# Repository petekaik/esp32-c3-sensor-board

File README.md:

# ESP32-C3 Sensor Carrier Board

Wall-mountable carrier for an **ESP32-C3 Super Mini** that exposes the module's GPIO, power and
comms for plug-in sensor and peripheral modules. Hardware only — the ESPHome configuration lives
in a separate project (`doorbell.yml` is the authoritative pin/feature map).

Current board: **rev2, 46 × 89 mm**, 2-layer, USB-C on the top short edge.

## Modules

| Function | Module | Interface | Address / settings |
|---|---|---|---|
| Temperature, humidity, pressure | BME280 (BME680 variant) | I²C, 1×6 socket | 0x76 (SDO → GND) |
| Illuminance | BH1750 (GY-302) | I²C, 1×5 socket | 0x23 (ADDR → GND) |
| Presence | HLK-LD2410C | UART, 1×5 socket | 256000 baud, 8N1 |
| Relay | KY-019 class | 1×3 right-angle socket | 5 V, active-high signal |
| Button | wire terminal | 2-pin screw terminal | to GND, internal pull-up |

Female sockets are fitted on the carrier; the modules carry male pins. Relay and button remain
screw/plug connections.

## Pin map (rev2)

| Function | ESP32-C3 pin | Net | Where |
|---|---|---|---|
| Relay control | GPIO4 | RELAY | J3 pin 3 |
| Button | GPIO3 | BUTTON | J4 pin 1 |
| I²C SDA | GPIO8 | I2C_SDA | J1/J2 + breakout |
| I²C SCL | GPIO9 | I2C_SCL | J1/J2 + breakout |
| LD2410C RX (module TX) | GPIO20 | UART_RX | U2 pin 1 |
| LD2410C TX (module RX) | GPIO21 | UART_TX | U2 pin 2 |
| SPI CS (jumper option) | GPIO7 | SPI_CS | JP1 pin 3 + breakout |
| SPI MISO (jumper option) | GPIO5 | SPI_MISO | JP2 pin 3 + breakout |
| SPI SCK / MOSI (SPI mode) | GPIO9 / GPIO8 | I2C_SCL / I2C_SDA | BME280 SCL/SDA — shared with I²C |

GPIO18/19 are the native USB pins and are left free for flashing/logging.

## Breakout row (J5, 1×14 female socket)

`3V3 · 5V · GND · GPIO0 · GPIO1 · GPIO2 · GPIO5 · GPIO6 · GPIO7 · GPIO10 · SDA · SCL · RX · TX`

J5 is fitted with a standard 2.54 mm 1×14 female socket
(`Connector_PinSocket_2.54mm:PinSocket_1x14_P2.54mm_Vertical`), so the board
can be ordered fully assembled.

I²C and UART are on the row by net name, so a second device can share the buses. I²C uses GPIO8/9,
which are also C3 strapping pins (GPIO9 = BOOT, GPIO8 = LED on most Super Minis); the module-side
I²C pull-ups hold both high at reset, which is the required state. GPIO0/GPIO2 are the other
strapping pins — usable as taps, but do not hold them low at reset. GPIO8 drives the onboard LED
as well, so expect faint LED activity during I²C traffic.

## Jumpers (2.54 mm headers, shunt-selectable)

| Ref | Pins | Default (doorbell.yml) | Function |
|---|---|---|---|
| JP1 | 1×3 | **1–2** | 1=3V3, 2=BME CSB, 3=SPI_CS (GPIO7) → 1–2 = I²C, 2–3 = SPI |
| JP2 | 1×3 | **1–2** | 1=GND, 2=BME SDO, 3=SPI_MISO (GPIO5) → 1–2 = 0x76, 2–3 = SPI MISO |
| JP3 | 1×2 | **1–2** | GND–ADDR → 0x23 (open = 0x5C) |

JP1/JP2 sit under the BME280 socket (≈6 mm clearance); the default 1–2 pair is ticked on the
bottom silkscreen, where the pins are numbered (1–3) and the JP1/JP2/JP3 columns are named.
The full descriptions are printed on the back.

## Variants / roadmap

| Variant | Size | Relay | Button | Sensor | Breakout | Status |
|---|---|---|---|---|---|---|
| [relay-bme280](docs/variants/relay-bme280.md) (rev2) | 46 × 89 | yes | J4 | BME280 | 1×14 | **built / ordered** |
| [relay-bme280](docs/variants/relay-bme280.md) (rev3) | 46 × 89 | yes | J4 | BME280 | 1×16 | **routed** |
| [relay-bme680](docs/variants/relay-bme680.md) (rev3) | 46 × 89 | yes | J4 | BME680 | 1×16 | **PCB ready** (sensor/firmware variant) |
| [compact-bme280](docs/variants/compact-bme280.md) (compact) | 34 × 76 | no | none | BME280 | 1×16 | **routed** |
| [compact-bme680](docs/variants/compact-bme680.md) (compact) | 34 × 76 | no | none | BME680 | 1×16 | **PCB ready** (sensor/firmware variant) |
| [slim-bme280](docs/variants/slim-bme280.md) (slim) | 42 × 84 | no | none | BME280 | 1×16 (DNP) | **routed** |

Rev3 expands J5 to a **1×16** row: `3V3 · 5V · GND · GPIO0 · GPIO1 · GPIO2 ·
GPIO3 · GPIO4 · GPIO5 · GPIO6 · GPIO7 · GPIO10 · SDA · SCL · RX · TX`. The
relay variants keep J3/J4 and expose GPIO3/GPIO4 on both the terminals and J5.
The compact board (`hardware/esp32-c3-sensor-board-compact.*`) drops **J3 and
J4**, removes the relay area, and is a **34 × 76 mm stacked column**: radar,
BH1750 rotated 90° to a landscape body, BME280 rotated 90° to a portrait body,
and J5 in the right-hand strip. It is 12 mm narrower than rev2 and uses the
same full 1×16 row.

The slim board (`hardware/esp32-c3-sensor-board-slim.*`) is a **42 × 84 mm**
take on the compact. Every module — including the ESP32-C3 — mounts on a
**right-angle (horizontal) female socket** soldered flat to the carrier, and
carries a 90° bent male pin row on its solder side. That makes a three-layer
stack (carrier / horizontal pins / module PCB) about **7.5 mm** high instead of
the 16.6 mm vertical-socket deck, at the cost of a wider carrier. The mounting
holes and the three through-hole jumpers are gone; BME280 CSB/SDO and BH1750
ADDR are hard-wired for I²C (0x76 / 0x23), and the 1×16 GPIO row is bare holes
(socket not fitted).

## Documentation

- [Pin map and connectors](docs/pinout.md)
- [Bill of materials](docs/BOM.csv)
- [Cost estimate — bare vs populated](docs/pricing.md) (script: `tools/aisler_quote.py`)
- [Generated HTML page](docs/index.html) (GitHub Pages ready)
- Variant pages under [`docs/variants/`](docs/variants/)

## Repository layout

```
hardware/                 KiCad 10 project (rev2), libraries, 3D models
docs/                     documentation, BOM, HTML page
doorbell.yml              authoritative ESPHome configuration
CLAUDE.md / HANDOFF.md    design brief and working notes
```

## Ordering

- 2-layer, 1.6 mm FR4, 0.25 mm minimum trace, 0.20 mm clearance, 0.8/0.3 mm vias
  (0.25 mm annular ring, untented with 0.9 mm mask openings), 50 µm solder-mask
  expansion, 0.15 mm silkscreen, ENIG preferred (castellated nothing — all standard PTH).
- Assembly is hand-solder: sockets, terminals, jumper headers, breakout row.
- Do not fit metal-filled or carbon filament anywhere in front of the radar or light sensor.

## Licence

Hardware design files: CERN-OHL-P-2.0 (proposed). Documentation: CC BY-SA 4.0.

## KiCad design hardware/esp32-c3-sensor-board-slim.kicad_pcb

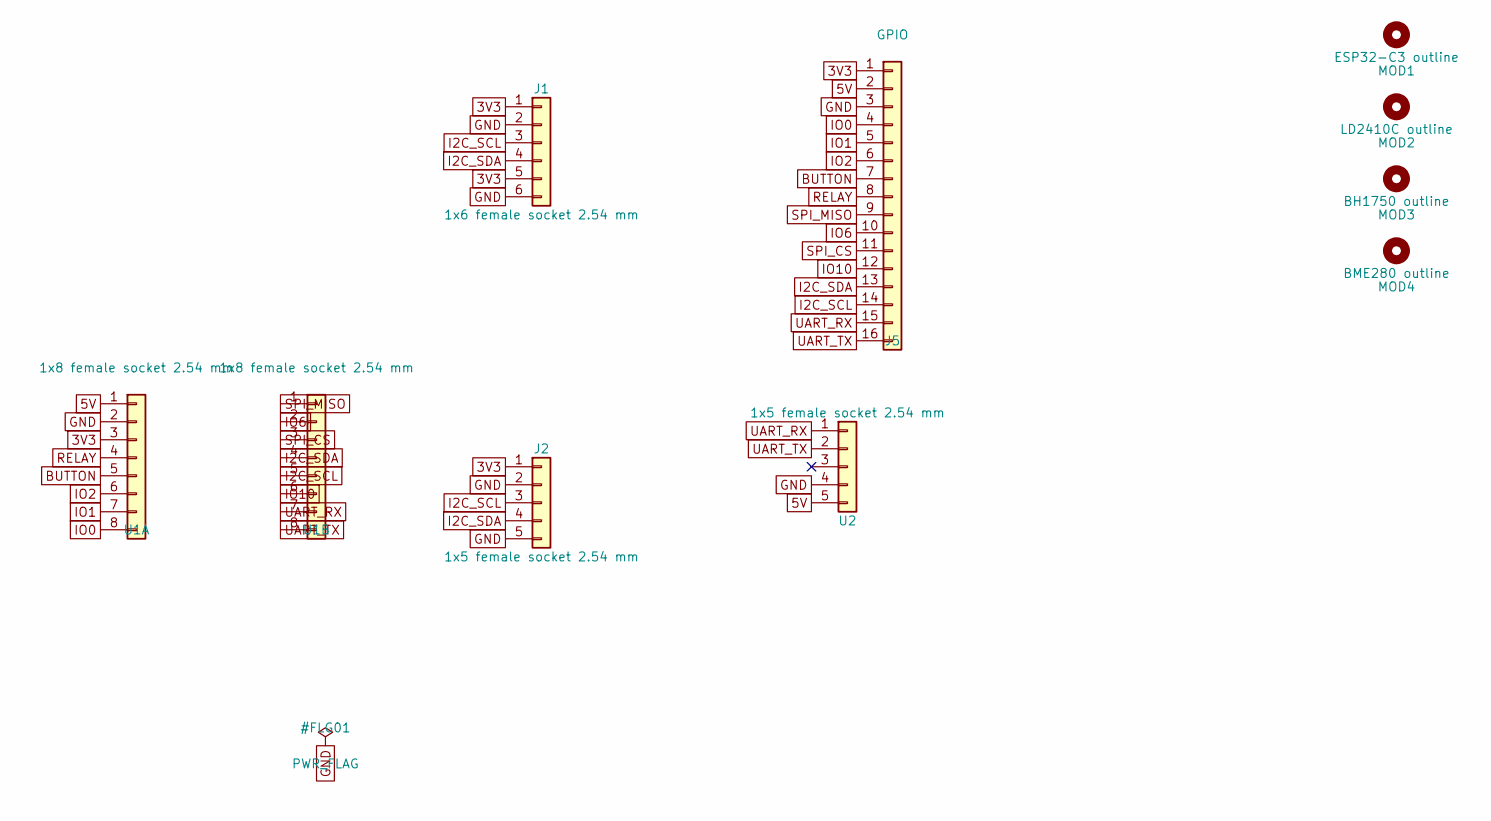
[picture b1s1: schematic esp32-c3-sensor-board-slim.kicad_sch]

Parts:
J1: 1x6 female socket 2.54 mm; PinSocket_1x06_P2.54mm_Horizontal_MirrorX_Rev; LCSC C40877
J2: 1x5 female socket 2.54 mm; PinSocket_1x05_P2.54mm_Horizontal_Rev; LCSC C50950
J5: GPIO; PinSocket_1x16_P2.54mm_Vertical; LCSC C7499334
MOD1: ESP32-C3 outline; module_outline_esp32c3
MOD2: LD2410C outline; module_outline_ld2410c
MOD3: BH1750 outline; module_outline_bh1750
MOD4: BME280 outline; module_outline_bme280
U1A, U1B: 1x8 female socket 2.54 mm; PinSocket_1x08_P2.54mm_Horizontal_MirrorX; LCSC C27438
U2: 1x5 female socket 2.54 mm; PinSocket_1x05_P2.54mm_Horizontal_Rev; LCSC C50950

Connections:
3V3: J1.1, J1.5, J2.1, J5.1, U1A.3
5V: J5.2, U1A.1, U2.5
BUTTON: J5.7, U1A.5
GND: J1.2, J1.6, J2.2, J2.5, J5.3, U1A.2, U2.4
I2C_SCL: J1.3, J2.3, J5.14, U1B.5
I2C_SDA: J1.4, J2.4, J5.13, U1B.4
IO0: J5.4, U1A.8
IO1: J5.5, U1A.7
IO2: J5.6, U1A.6
IO6: J5.10, U1B.2
IO10: J5.12, U1B.6
RELAY: J5.8, U1A.4
SPI_CS: J5.11, U1B.3
SPI_MISO: J5.9, U1B.1
UART_RX: J5.15, U1B.7, U2.1
UART_TX: J5.16, U1B.8, U2.2

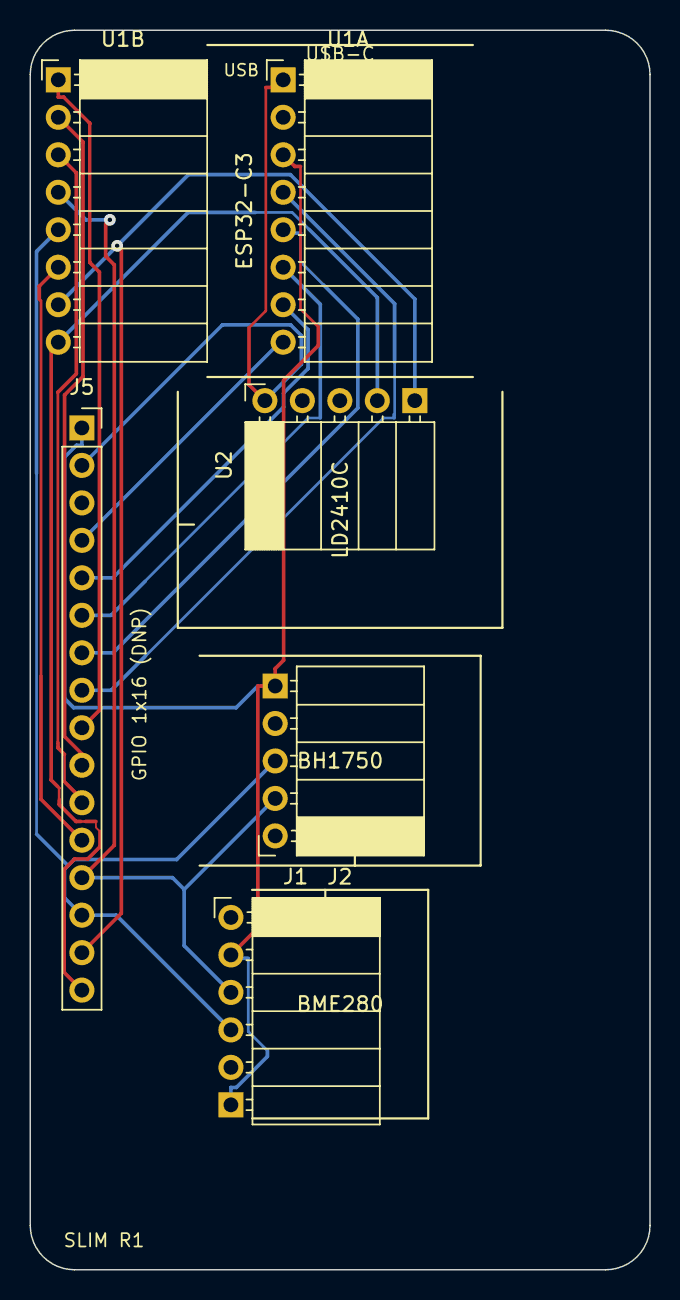
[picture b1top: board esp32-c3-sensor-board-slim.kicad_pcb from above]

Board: 2 copper layers, 42.0 x 84.0 mm, 10 parts (0 on the bottom side), 16 nets.

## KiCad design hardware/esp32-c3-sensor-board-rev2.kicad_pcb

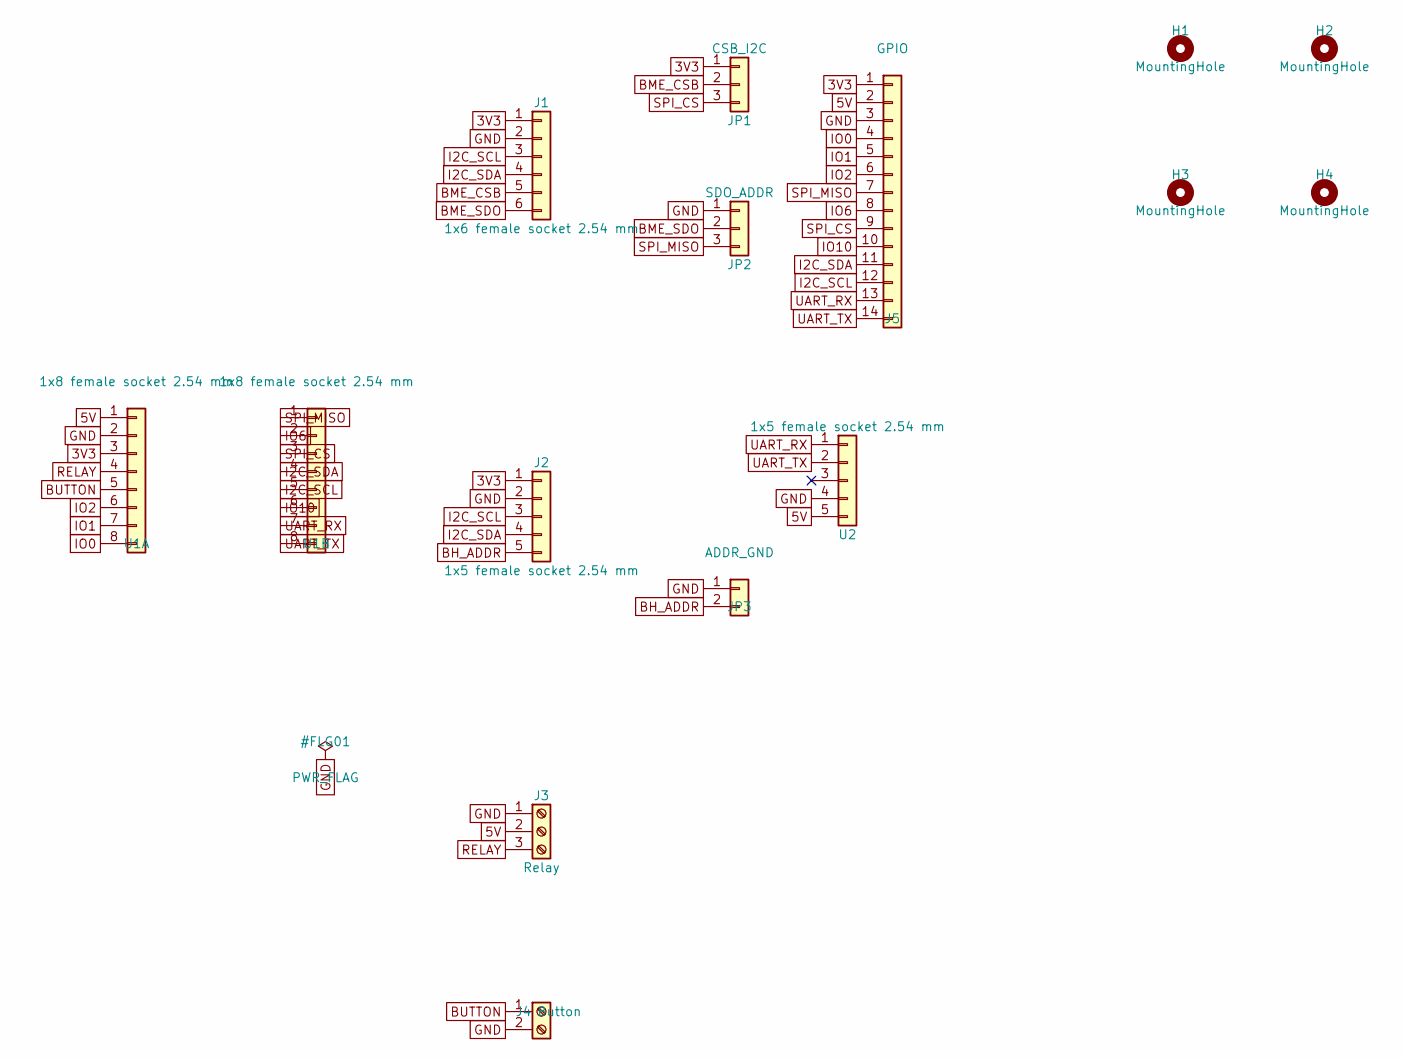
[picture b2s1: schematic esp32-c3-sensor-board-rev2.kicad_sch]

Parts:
H1, H2, H3, H4: MountingHole; MountingHole_3.2mm_M3
J1: 1x6 female socket 2.54 mm; PinSocket_1x06_P2.54mm_Vertical; LCSC C40877
J2: 1x5 female socket 2.54 mm; PinSocket_1x05_P2.54mm_Vertical; LCSC C50950
J3: Relay; PinSocket_1x03_P2.54mm_Horizontal; LCSC C54876732
J4: Button; TerminalBlock_MaiXu_MX126-5.0-02P_1x02_P5.00mm; LCSC C5188434
J5: GPIO; PinSocket_1x14_P2.54mm_Vertical; LCSC C41417326
JP1: CSB_I2C; PinHeader_1x03_P2.54mm_Vertical; LCSC C49257
JP2: SDO_ADDR; PinHeader_1x03_P2.54mm_Vertical; LCSC C49257
JP3: ADDR_GND; PinHeader_1x02_P2.54mm_Vertical; LCSC C32713268
U1A, U1B: 1x8 female socket 2.54 mm; PinSocket_1x08_P2.54mm_Vertical; LCSC C27438
U2: 1x5 female socket 2.54 mm; ld2410c; LCSC C50950

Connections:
3V3: J1.1, J2.1, J5.1, JP1.1, U1A.3
5V: J3.2, J5.2, U1A.1, U2.5
BH_ADDR: J2.5, JP3.2
BME_CSB: J1.5, JP1.2
BME_SDO: J1.6, JP2.2
BUTTON: J4.1, U1A.5
GND: J1.2, J2.2, J3.1, J4.2, J5.3, JP2.1, JP3.1, U1A.2, U2.4
I2C_SCL: J1.3, J2.3, J5.12, U1B.5
I2C_SDA: J1.4, J2.4, J5.11, U1B.4
IO0: J5.4, U1A.8
IO1: J5.5, U1A.7
IO2: J5.6, U1A.6
IO6: J5.8, U1B.2
IO10: J5.10, U1B.6
RELAY: J3.3, U1A.4
SPI_CS: J5.9, JP1.3, U1B.3
SPI_MISO: J5.7, JP2.3, U1B.1
UART_RX: J5.13, U1B.7, U2.1
UART_TX: J5.14, U1B.8, U2.2

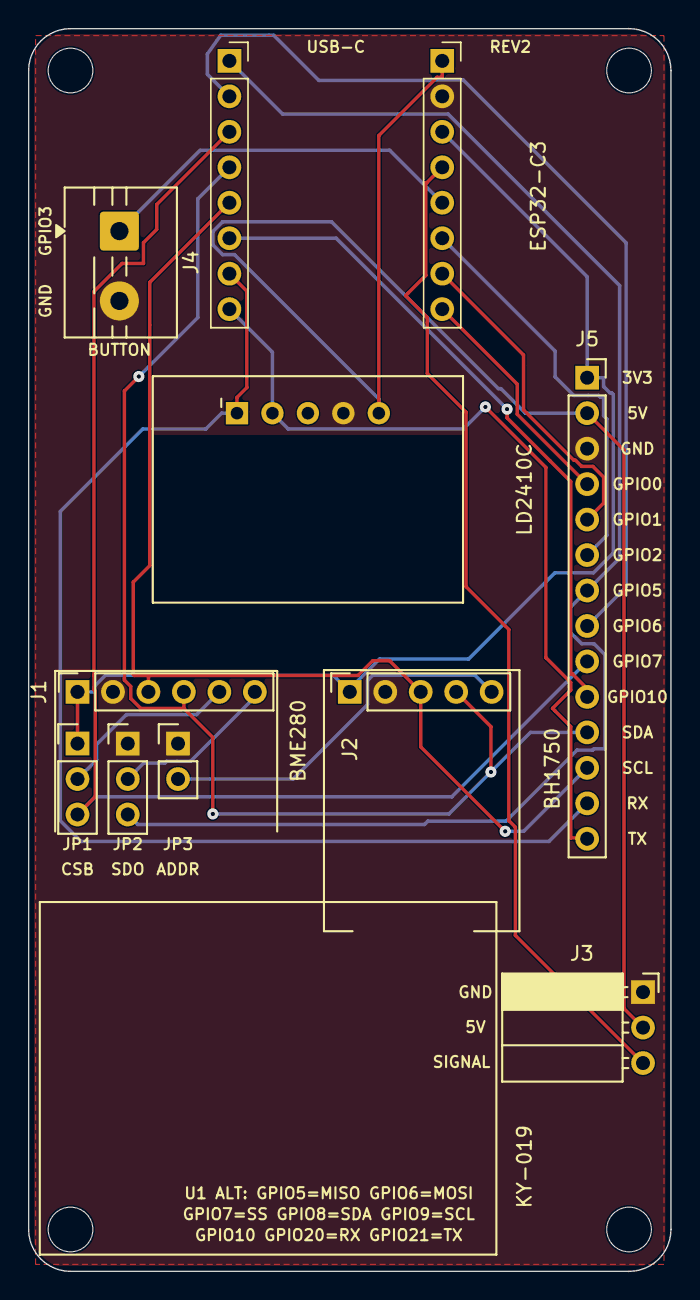
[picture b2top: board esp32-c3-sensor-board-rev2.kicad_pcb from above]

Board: 2 copper layers, 46.0 x 89.0 mm, 15 parts (0 on the bottom side), 19 nets.

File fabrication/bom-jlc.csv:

Designator,Footprint,Quantity,Value,LCSC Part #
J1,PinSocket_1x06_P2.54mm_Vertical,1,1x6 female socket 2.54 mm,C40877
J2,PinSocket_1x05_P2.54mm_Vertical,1,1x5 female socket 2.54 mm,C50950
J4,TerminalBlock_MaiXu_MX126-5.0-02P_1x02_P5.00mm,1,Button,C5188434
J5,PinSocket_1x14_P2.54mm_Vertical,1,GPIO,C41417326
JP1,PinHeader_1x03_P2.54mm_Vertical,1,CSB_I2C,C49257
JP2,PinHeader_1x03_P2.54mm_Vertical,1,SDO_ADDR,C49257
JP3,PinHeader_1x02_P2.54mm_Vertical,1,ADDR_GND,C32713268
"U1A, U1B",PinSocket_1x08_P2.54mm_Vertical,2,1x8 female socket 2.54 mm,C27438
U2,ld2410c,1,1x5 female socket 2.54 mm,C50950

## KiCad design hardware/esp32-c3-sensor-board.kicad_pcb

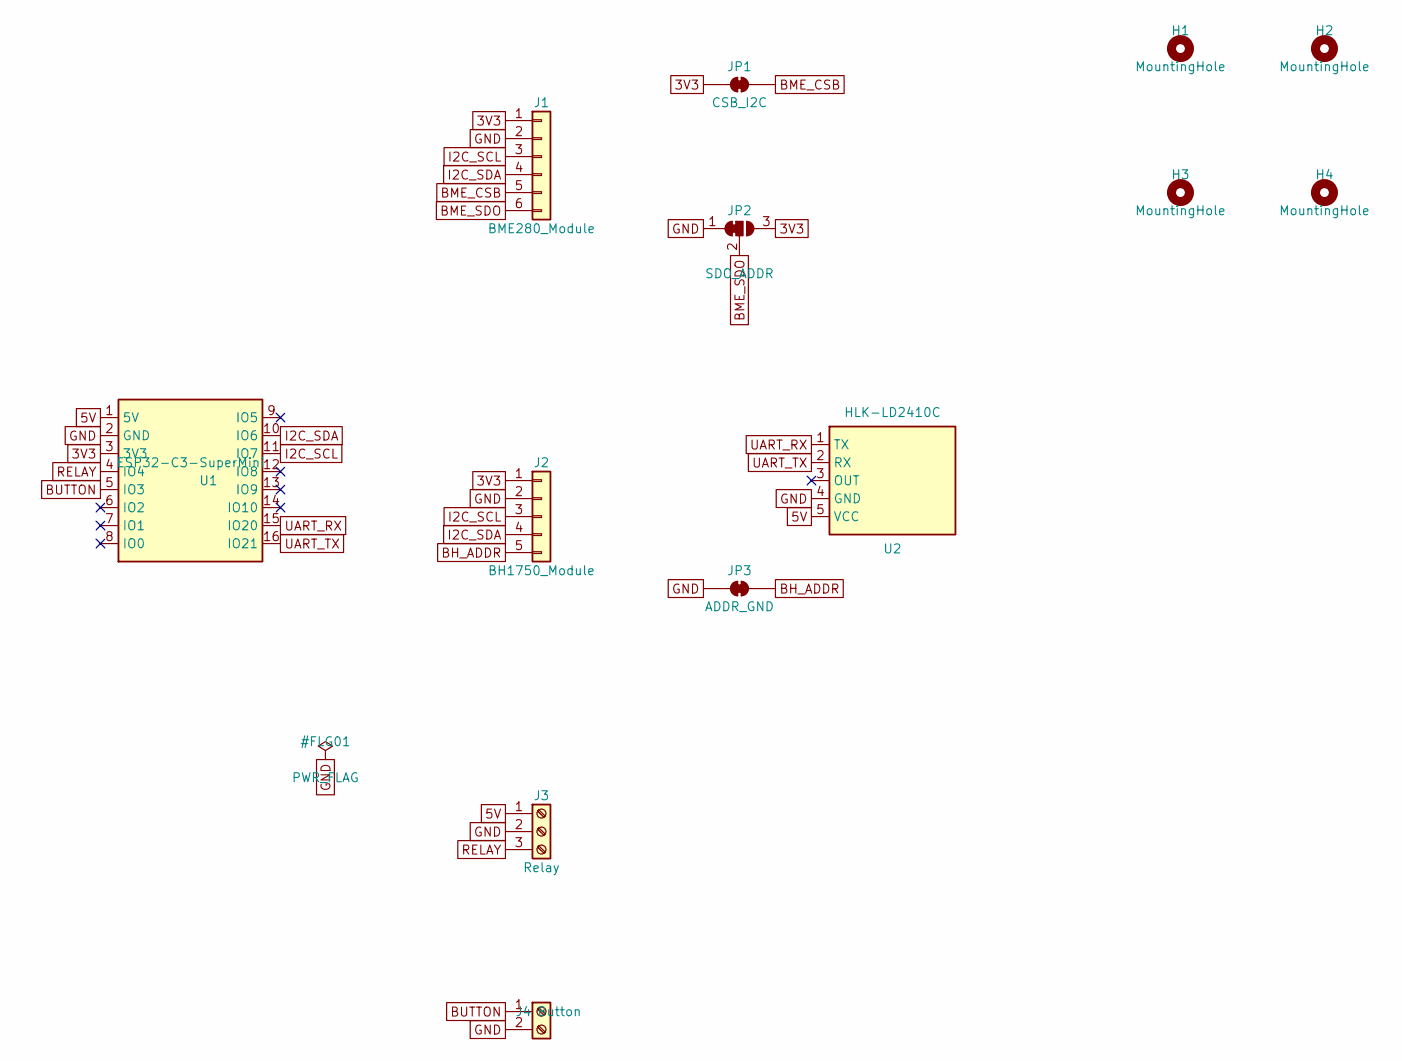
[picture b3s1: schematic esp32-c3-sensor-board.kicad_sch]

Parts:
H1, H2, H3, H4: MountingHole; MountingHole_3.2mm_M3
J1: BME280_Module; PinSocket_1x06_P2.54mm_Vertical
J2: BH1750_Module; PinSocket_1x05_P2.54mm_Vertical
J3: Relay; TerminalBlock_MaiXu_MX126-5.0-03P_1x03_P5.00mm
J4: Button; TerminalBlock_MaiXu_MX126-5.0-02P_1x02_P5.00mm
JP1: CSB_I2C; SolderJumper-2_P1.3mm_Bridged_RoundedPad1.0x1.5mm
JP2: SDO_ADDR; SolderJumper-3_P1.3mm_Bridged12_RoundedPad1.0x1.5mm
JP3: ADDR_GND; SolderJumper-2_P1.3mm_Bridged_RoundedPad1.0x1.5mm
U1: ESP32-C3-SuperMini; ESP32-C3-SuperMini_Socket
U2: HLK-LD2410C; ld2410c

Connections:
3V3: J1.1, J2.1, JP1.1 (A), JP2.3 (B), U1.3 (3V3)
5V: J3.1, U1.1 (5V), U2.5 (VCC)
BH_ADDR: J2.5, JP3.2 (B)
BME_CSB: J1.5, JP1.2 (B)
BME_SDO: J1.6, JP2.2 (C)
BUTTON: J4.1, U1.5 (IO3)
GND: J1.2, J2.2, J3.2, J4.2, JP2.1 (A), JP3.1 (A), U1.2 (GND), U2.4 (GND)
I2C_SCL: J1.3, J2.3, U1.11 (IO7)
I2C_SDA: J1.4, J2.4, U1.10 (IO6)
RELAY: J3.3, U1.4 (IO4)
UART_RX: U1.15 (IO20), U2.1 (TX)
UART_TX: U1.16 (IO21), U2.2 (RX)

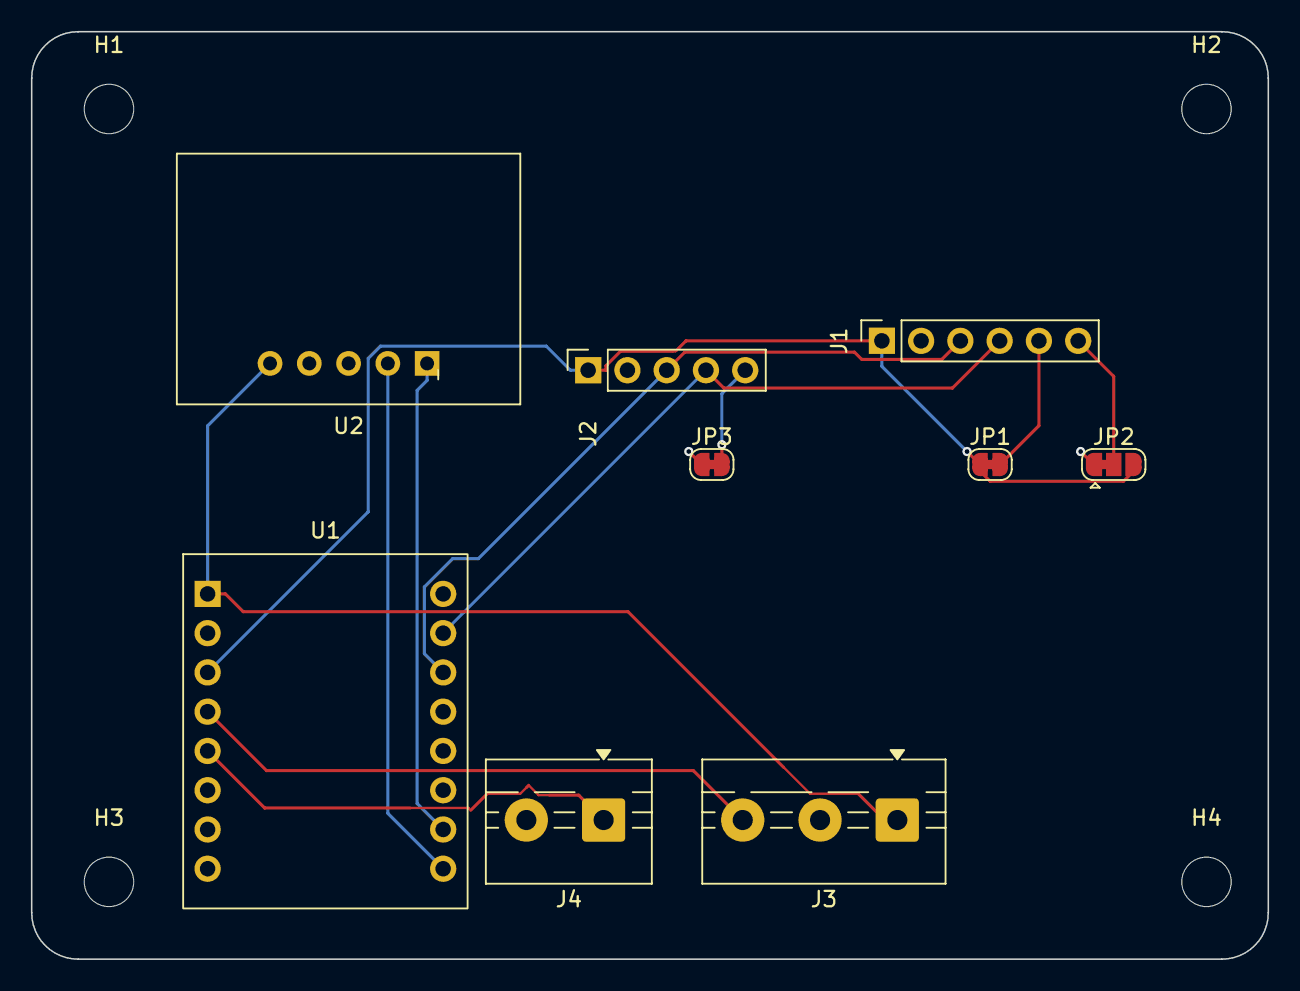
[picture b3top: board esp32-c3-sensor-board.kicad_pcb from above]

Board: 2 copper layers, 80.0 x 60.0 mm, 13 parts (0 on the bottom side), 12 nets.
